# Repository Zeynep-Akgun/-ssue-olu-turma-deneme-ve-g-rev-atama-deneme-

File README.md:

# -ssue-olu-turma-deneme-ve-g-rev-atama-deneme-
İssue oluşturma ve görev atama deneme

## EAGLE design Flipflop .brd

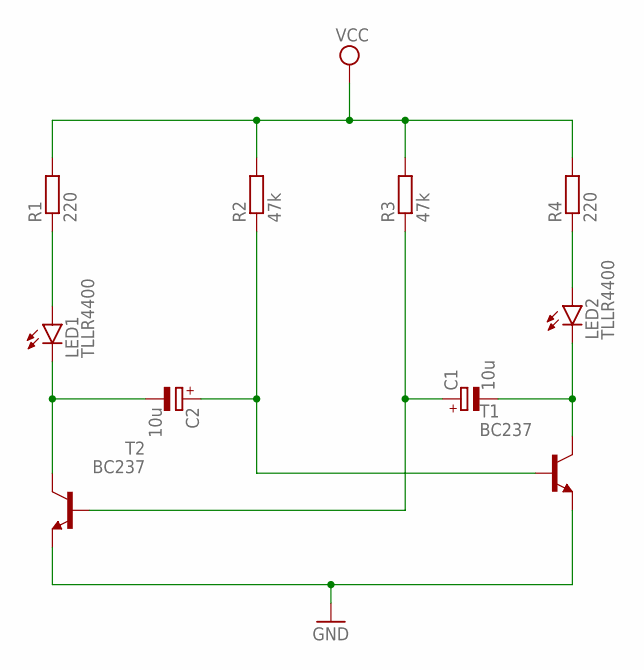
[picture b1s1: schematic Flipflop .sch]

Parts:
C1, C2: 10u; 140CLH-1014
LED1, LED2: TLLR4400; LED3MM
R1, R4: 220; 0207/12
R2, R3: 47k; 0207/12
T1, T2: BC237; TO92

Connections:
GND: T1.1 (E), T2.1 (E)
unnamed: LED1.A, R1.1
unnamed: C2.-, LED1.K (C), T2.3 (C)
unnamed: LED2.A, R4.1
unnamed: C1.-, LED2.K (C), T1.3 (C)
unnamed: C1.+, R3.1, T2.2 (B)
unnamed: C2.+, R2.1, T1.2 (B)
VCC: R1.2, R2.2, R3.2, R4.2

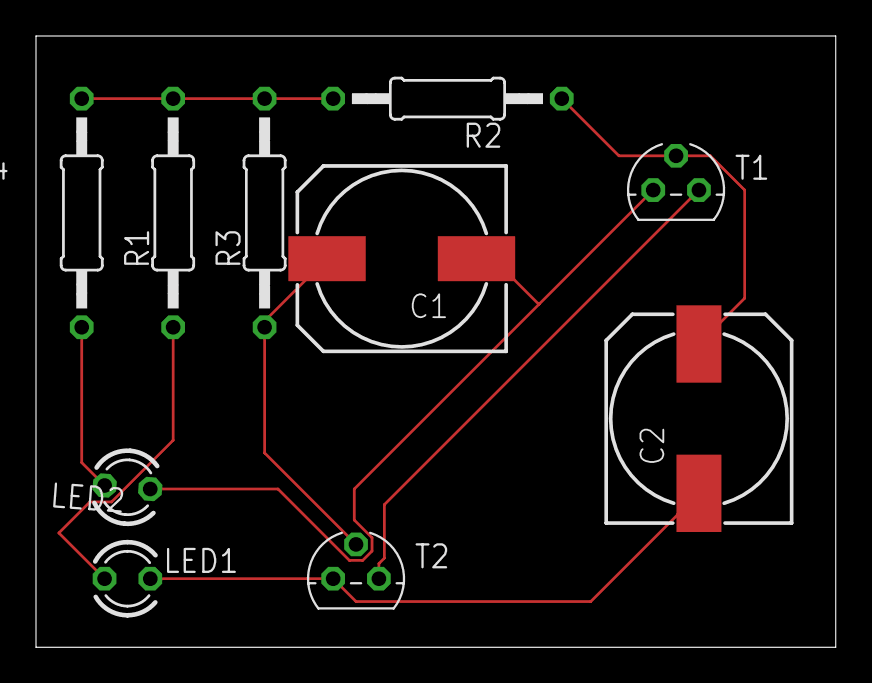
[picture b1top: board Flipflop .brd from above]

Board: 2 copper layers, 44.4 x 34.0 mm, 10 parts (0 on the bottom side), 8 nets.
